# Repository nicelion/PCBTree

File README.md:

# PCBTree
A Christmas tree shaped circuit board that every nerd will love!

## About
PCBTree fills it's name quite well as it is, exactly what it says: A PCB tree. The Christmas tree shaped printed circuit board is populated with 6 green LEDs and 6 red LEDs and two yellow LEDs, all controlled by an ATTiny85 to allow the red and green LEDs to flash to you liking.

## Instruction

### How to operate
If you were given a PCBTree, below is some basic information on how it can be used.

#### Plugging In and Turning On
To first turn on PCBTree, one must plug in the provided 5V AC-DC adapter into the barrel jack connector located on the beck of the device, and into the wall. 

Once this is done, the switch on the back of the device must also be switched to the "on" state, and PCBTree will then turn on.

#### Adjusting Blink Speed
A dial, professionally, a potentiometer, can be found on the base, towards the front. This dial can be used to adjust the speed the LEDs will flash. The equation is below:

<p align="center">
  
  <br>
  
</p>

The potentiometer give the microcontroller a value, between 50 and 500, and the delay between the flashing will be the potentiometer value, multiplied by 1.25 in miliseconds.

For example, if the potentiometer result is 300, the delay between the flashes will be 375 miliseconds.

However, if the potentiometer's value is 50, or all the way off, the red and green LEDs will not flash and if the potetiometer returns 500, then the red and green LEDs will shine constantly. The yellow star led will shine always unless the unit is turned off.

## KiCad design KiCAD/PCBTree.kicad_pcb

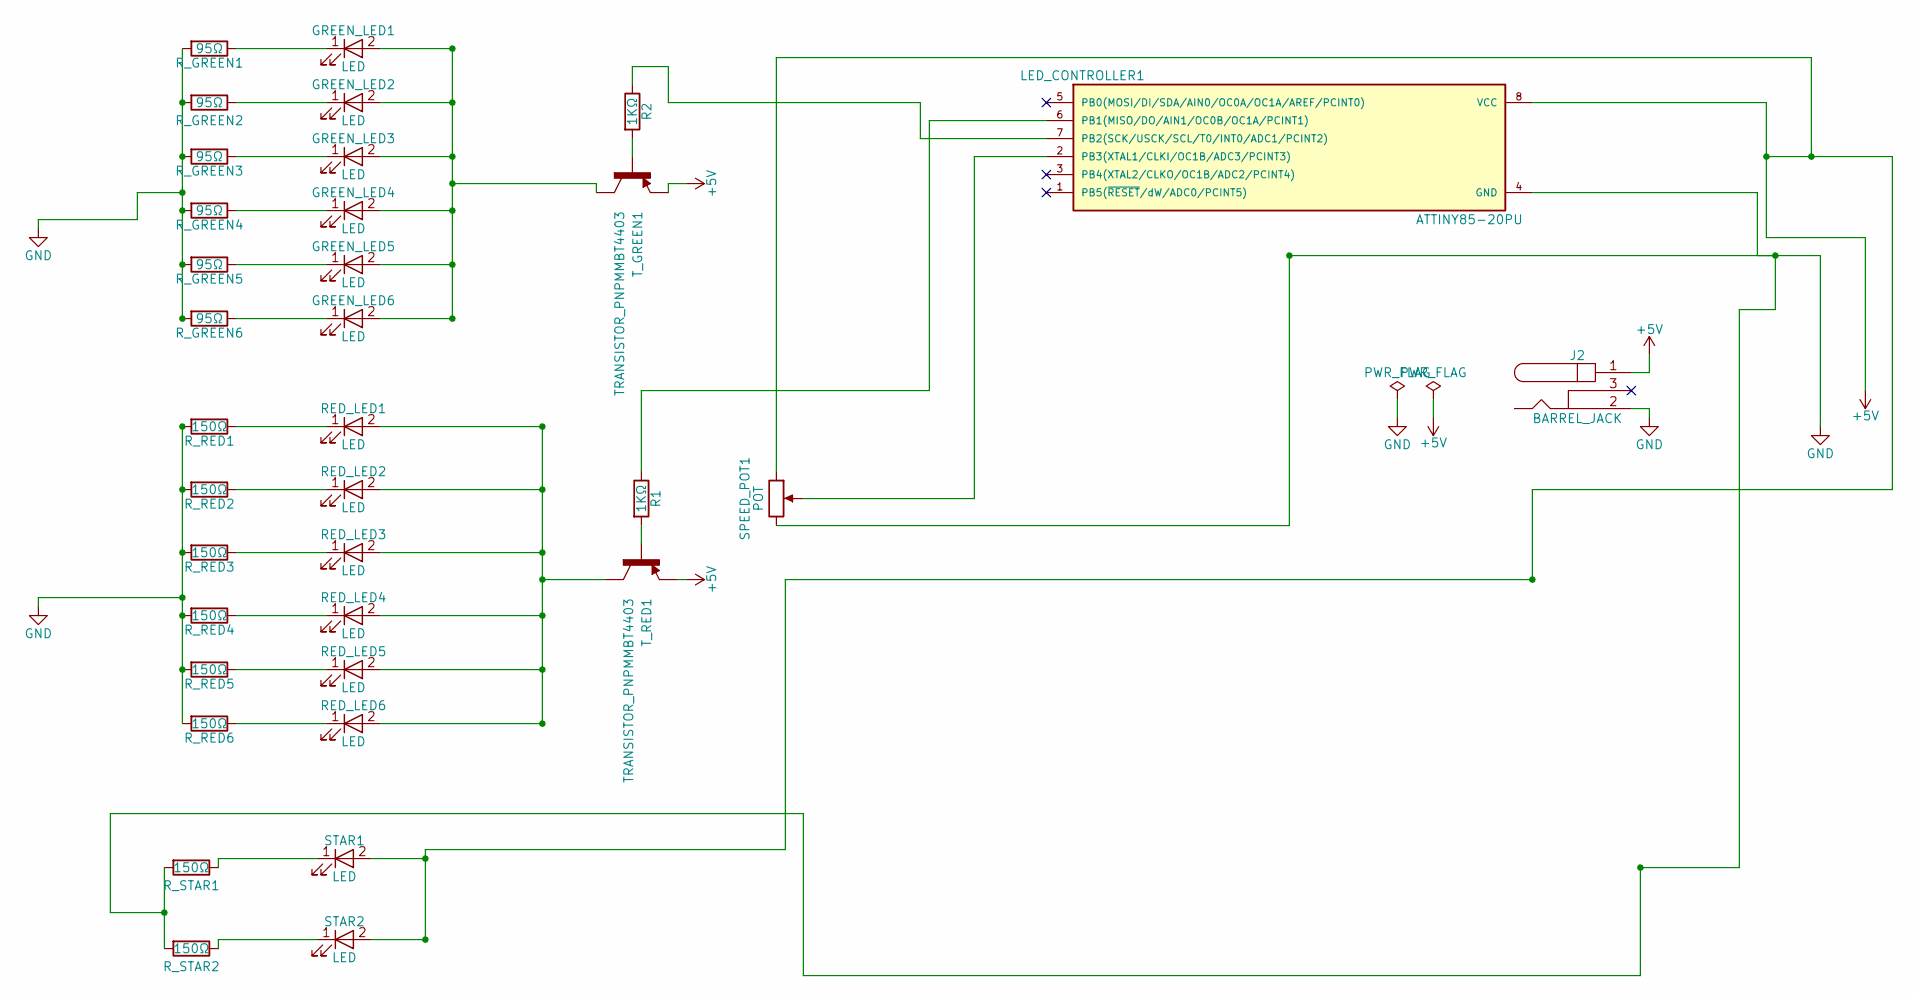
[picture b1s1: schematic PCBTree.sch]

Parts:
GREEN_LED1, GREEN_LED2, GREEN_LED3, GREEN_LED4, GREEN_LED5, GREEN_LED6: LED; LED_1206_HandSoldering
J2: BARREL_JACK
LED_CONTROLLER1: ATTINY85-20PU; DIP-8_W7.62mm_SMD
R1, R2: 1KΩ; R_1206_HandSoldering
RED_LED1, RED_LED2, RED_LED3, RED_LED4, RED_LED5, RED_LED6: LED; LED_1206_HandSoldering
R_GREEN1, R_GREEN2, R_GREEN3, R_GREEN4, R_GREEN5, R_GREEN6: 95Ω; R_1206_HandSoldering
R_RED1, R_RED2, R_RED3, R_RED4, R_RED5, R_RED6: 150Ω; R_1206_HandSoldering
R_STAR1, R_STAR2: 150Ω; R_1206_HandSoldering
SPEED_POT1: POT; PINHEAD1-3
STAR1, STAR2: LED; LED_1206_HandSoldering
T_GREEN1: TRANSISTOR_PNPMMBT4403; SOT-23_Handsoldering
T_RED1: TRANSISTOR_PNPMMBT4403; SOT-23_Handsoldering

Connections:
+5V: J2.1, LED_CONTROLLER1.8 (VCC), SPEED_POT1.1, STAR1.2 (A), STAR2.2 (A), T_GREEN1.2 (E), T_RED1.2 (E); also elsewhere on the board
GND: J2.2, LED_CONTROLLER1.4 (GND), R_GREEN1.2, R_GREEN2.2, R_GREEN3.2, R_GREEN4.2, R_GREEN5.2, R_GREEN6.2, R_RED1.2, R_RED2.2, R_RED3.2, R_RED4.2, R_RED5.2, R_RED6.2, R_STAR1.2, R_STAR2.2, SPEED_POT1.3; also elsewhere on the board
unnamed: GREEN_LED1.1 (K), R_GREEN1.1
unnamed 3: GREEN_LED1.2 (A), GREEN_LED2.2 (A), GREEN_LED3.2 (A), GREEN_LED4.2 (A), GREEN_LED5.2 (A), GREEN_LED6.2 (A), T_GREEN1.3 (C); also elsewhere on the board
unnamed: GREEN_LED2.1 (K), R_GREEN2.1
unnamed: GREEN_LED3.1 (K), R_GREEN3.1
unnamed: GREEN_LED4.1 (K), R_GREEN4.1
unnamed: GREEN_LED5.1 (K), R_GREEN5.1
unnamed: GREEN_LED6.1 (K), R_GREEN6.1
unnamed 11: LED_CONTROLLER1.2 (PB3(XTAL1/CLKI/OC1B/ADC3/PCINT3)), SPEED_POT1.2; also elsewhere on the board
unnamed 13: LED_CONTROLLER1.6 (PB1(MISO/DO/AIN1/OC0B/OC1A/PCINT1)), R1.1; also elsewhere on the board
unnamed 14: LED_CONTROLLER1.7 (PB2(SCK/USCK/SCL/T0/INT0/ADC1/PCINT2)), R2.1; also elsewhere on the board
unnamed: R1.2, T_RED1.1 (B)
unnamed: R2.2, T_GREEN1.1 (B)
unnamed: RED_LED1.1 (K), R_RED1.1
unnamed: RED_LED1.2 (A), RED_LED2.2 (A), RED_LED3.2 (A), RED_LED4.2 (A), RED_LED5.2 (A), RED_LED6.2 (A), T_RED1.3 (C)
unnamed: RED_LED2.1 (K), R_RED2.1
unnamed: RED_LED3.1 (K), R_RED3.1
unnamed: RED_LED4.1 (K), R_RED4.1
unnamed: RED_LED5.1 (K), R_RED5.1
unnamed: RED_LED6.1 (K), R_RED6.1
unnamed: R_STAR1.1, STAR1.1 (K)
unnamed: R_STAR2.1, STAR2.1 (K)

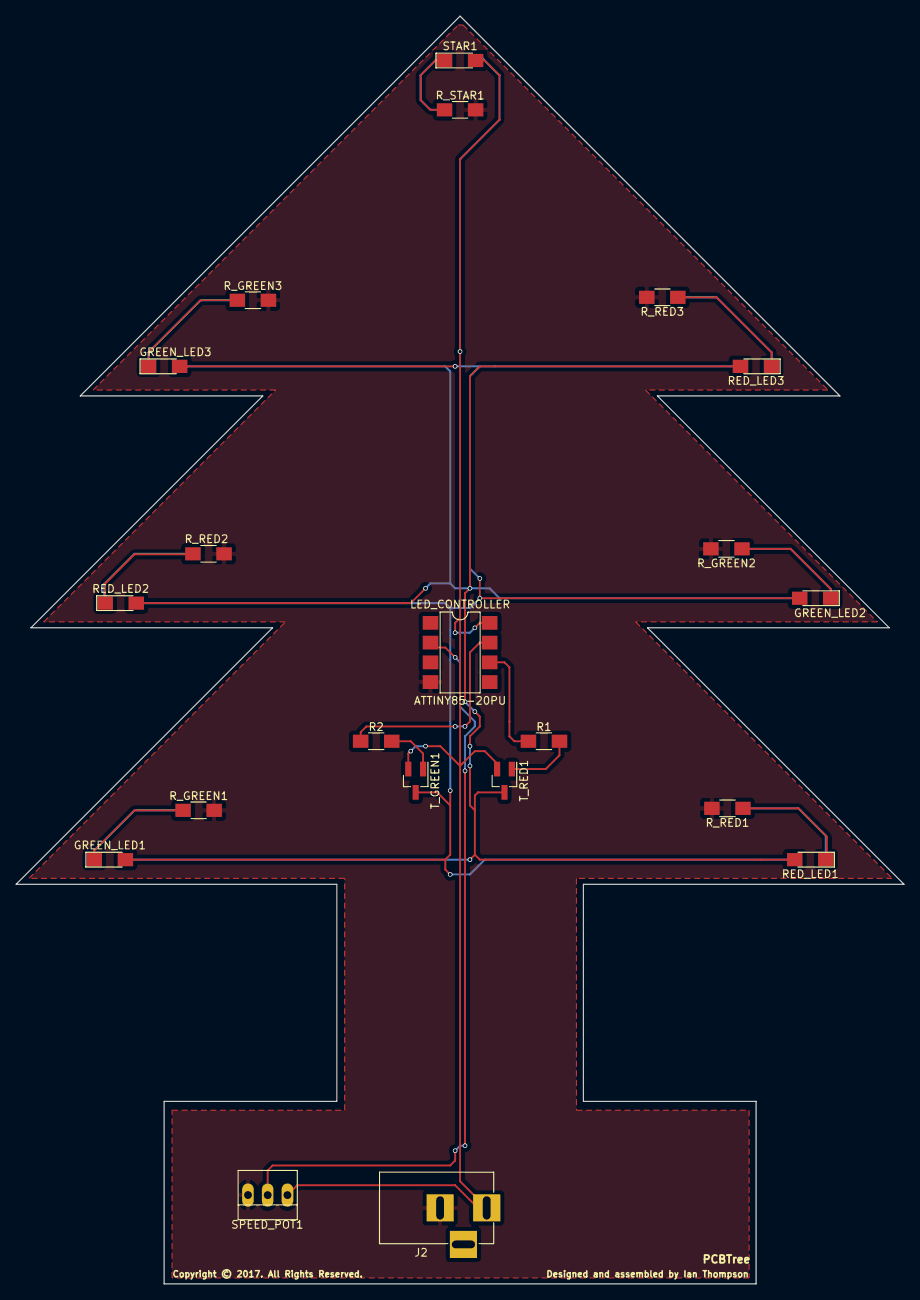
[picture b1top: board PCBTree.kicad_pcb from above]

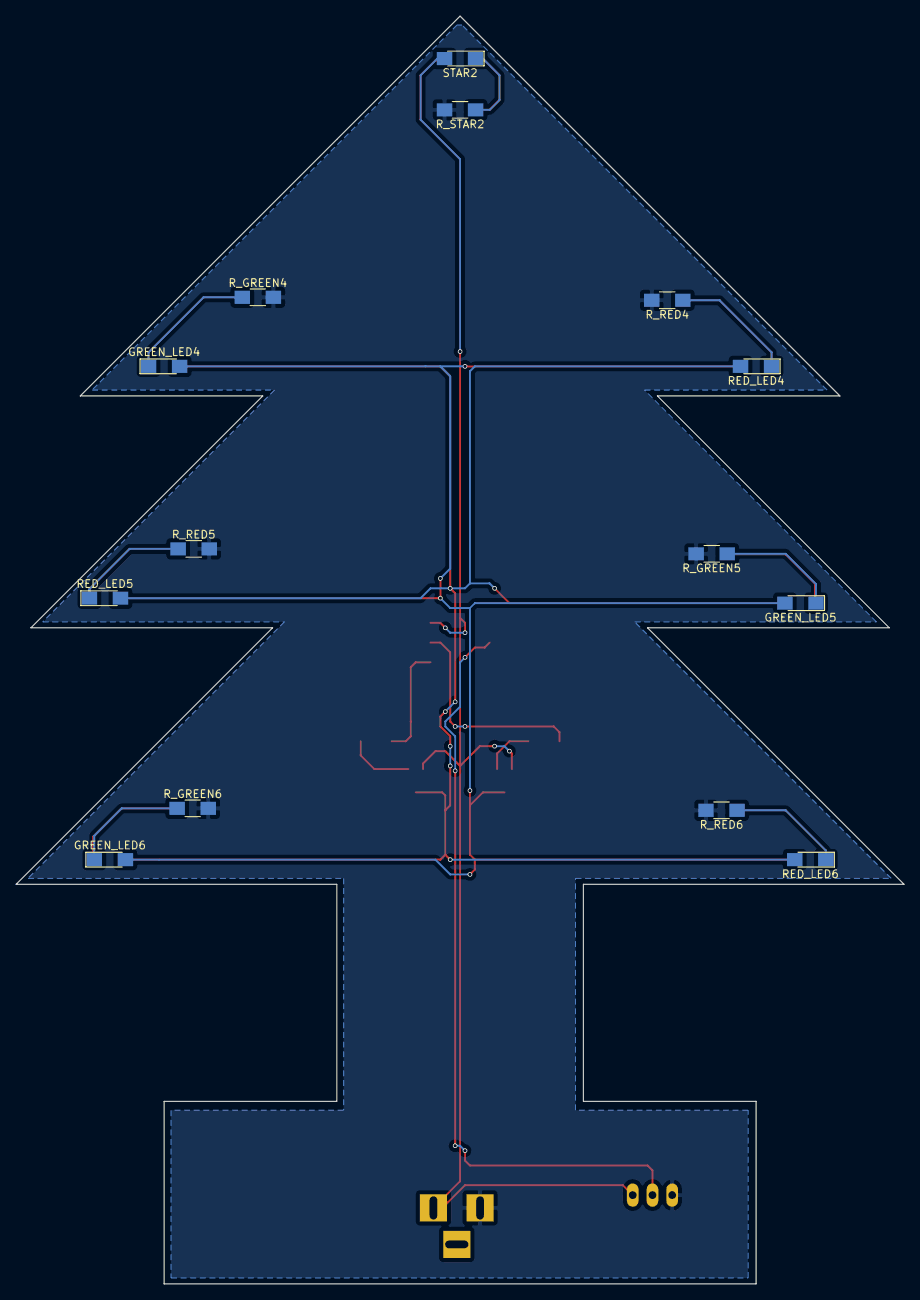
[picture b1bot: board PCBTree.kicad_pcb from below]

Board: 2 copper layers, 114.3 x 163.2 mm, 35 parts (14 on the bottom side), 23 nets.

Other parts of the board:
LED_CONTROLLER: ATTINY85-20PU; DIP-8_W7.62mm_SMD

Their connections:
+5V: LED_CONTROLLER.8; also elsewhere on the board
GND: LED_CONTROLLER.4; also elsewhere on the board
unnamed 3: LED_CONTROLLER.5; also elsewhere on the board
unnamed 11: LED_CONTROLLER.2; also elsewhere on the board
unnamed 13: LED_CONTROLLER.6; also elsewhere on the board
unnamed 14: LED_CONTROLLER.7; also elsewhere on the board

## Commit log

2017-11-30 Set theme jekyll-theme-minimal
2017-11-30 added img
2017-12-01 Set theme jekyll-theme-dinky
2017-12-01 Create LICENSE

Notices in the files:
KiCAD/PCBTree.kicad_pcb:
Copyright © 2017. All Rights Reserved.
